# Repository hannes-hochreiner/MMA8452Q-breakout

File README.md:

# MMA8452Q-breakout
A breakout board for the MMA8452Q 3-axis accelerometer

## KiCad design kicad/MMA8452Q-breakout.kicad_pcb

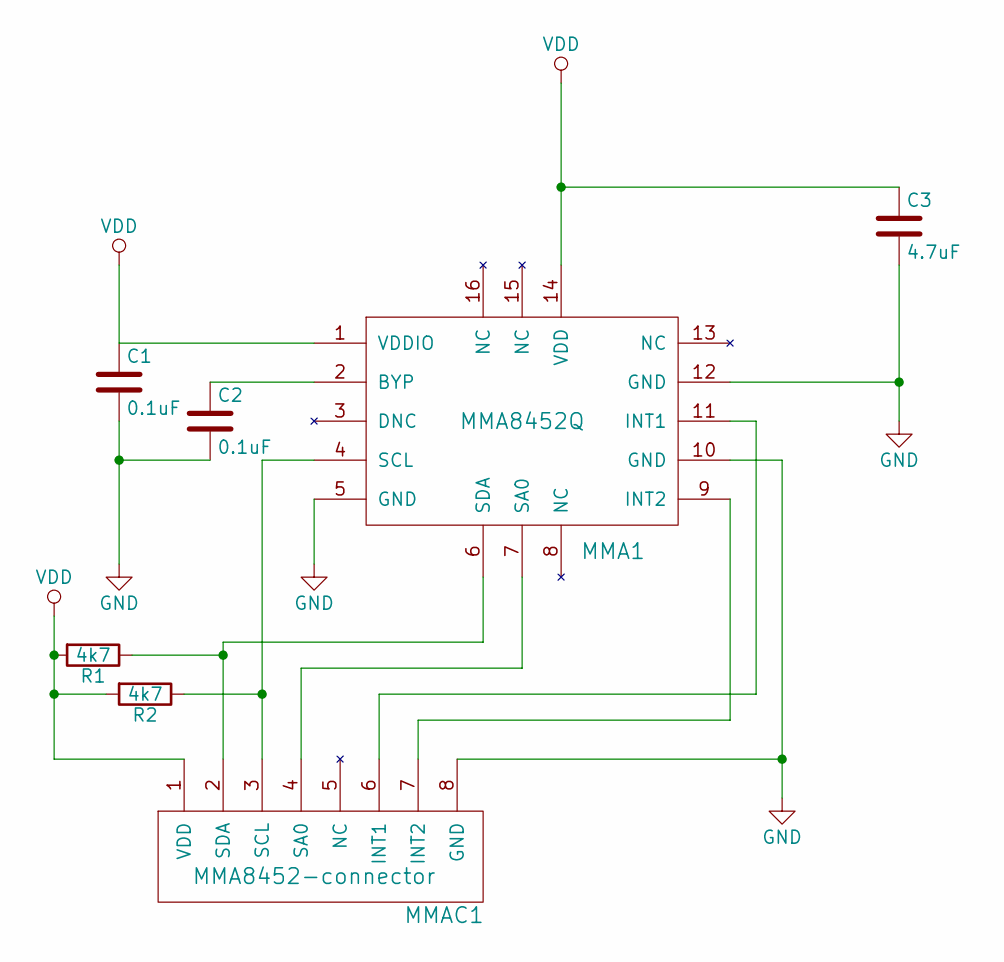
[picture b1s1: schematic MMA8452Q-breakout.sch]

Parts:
C1, C2: 0.1uF; C_0603_HandSoldering
C3: 4.7uF; C_0603_HandSoldering
MMA1: MMA8452Q
MMAC1: MMA8452-connector; MMA8452Q-connector
R1, R2: 4k7; R_0603_HandSoldering

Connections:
GND: C1.2, C2.2, C3.2, MMA1.5 (GND), MMA1.10 (GND), MMA1.12 (GND), MMAC1.8 (GND)
unnamed: C2.1, MMA1.2 (BYP)
unnamed: MMA1.4 (SCL), MMAC1.3 (SCL), R2.1
unnamed: MMA1.6 (SDA), MMAC1.2 (SDA), R1.1
unnamed: MMA1.7 (SA0), MMAC1.4 (SA0)
unnamed: MMA1.9 (INT2), MMAC1.7 (INT2)
unnamed: MMA1.11 (INT1), MMAC1.6 (INT1)
VDD: C1.1, C3.1, MMA1.1 (VDDIO), MMA1.14 (VDD), MMAC1.1 (VDD), R1.2, R2.2

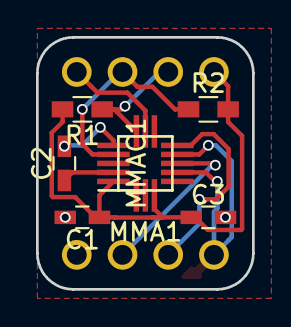
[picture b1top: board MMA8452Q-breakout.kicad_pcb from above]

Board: 2 copper layers, 12.0 x 14.0 mm, 7 parts (0 on the bottom side), 8 nets.

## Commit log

2018-02-18 initial version of the board
